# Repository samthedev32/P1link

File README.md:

# P1link
Cellural (NB-IoT) P1 Port Reader

## Hardware

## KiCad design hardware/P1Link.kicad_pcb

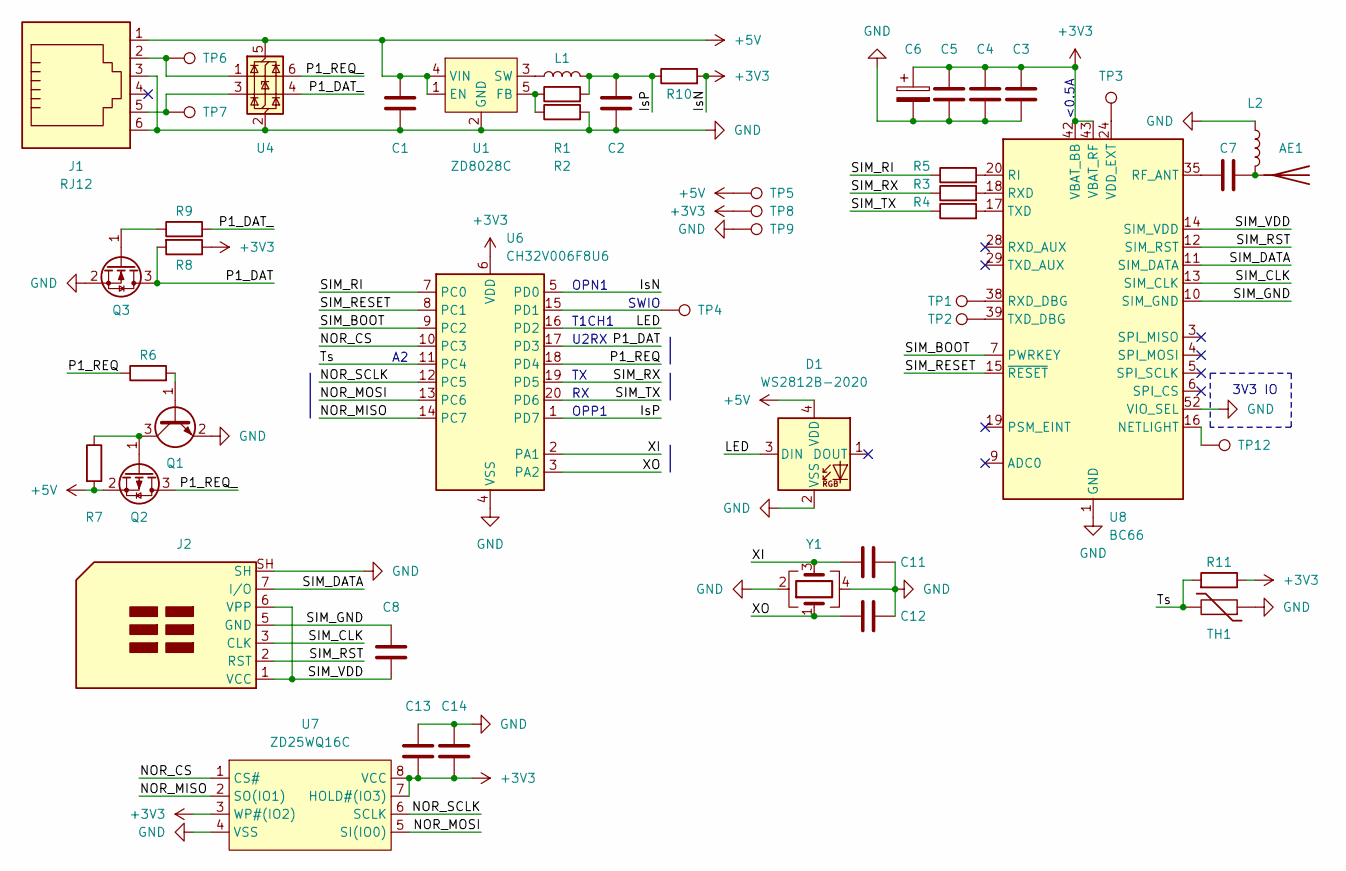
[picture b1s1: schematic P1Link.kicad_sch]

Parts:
AE1: Antenna; Texas_SWRA416_868MHz_915MHz
C1, C2, C14: 10u; C_0402_1005Metric
C3: 22p; C_0402_1005Metric
C4, C5: 100p; C_0402_1005Metric
C6: 100u; C_1206_3216Metric
C7: 1p; C_0402_1005Metric
C8, C13: 100n; C_0402_1005Metric
C11, C12: 8p; C_0402_1005Metric
D1: WS2812B-2020; LED_WS2812B-2020_PLCC4_2.0x2.0mm; JLCPCB Part# C965555
J1: RJ12; RJ25_Wayconn_MJEA-660X1_Horizontal; JLCPCB Part# C77859
J2: SIM_Card_Shielded; XUNPU_SMN-305; JLCPCB Part# C720512
L1: 4.7u; L_0402_1005Metric
L2: 12n; L_0402_1005Metric
Q1: Q_NPN_BEC; SOT-23; JLCPCB Part# C39280
Q2: Q_PMOS_GSD; SOT-23; JLCPCB Part# C5261052
Q3: Q_NMOS_GSD; SOT-23; JLCPCB Part# C4748714
R1: 261k; R_0402_1005Metric
R2: 59k; R_0402_1005Metric
R3, R4, R5: 1k; R_0402_1005Metric
R6: 1k - 10k; R_0402_1005Metric
R7: 10k - 100k; R_0402_1005Metric
R8: 4.7k - 10k; R_0402_1005Metric
R9: 100-1k; R_0402_1005Metric
R10: 100m; R_0402_1005Metric; JLCPCB Part# C1882657
R11: 10k; R_0402_1005Metric
TH1: 10k; R_0402_1005Metric; JLCPCB Part# C89601
TP1: RXD_DBG; TestPoint_Pad_D1.0mm
TP2: TXD_DBG; TestPoint_Pad_D1.0mm
TP3: VDD_EXT; TestPoint_Pad_D1.0mm
TP4: SWIO; TestPoint_Pad_D1.0mm
TP5: 5V; TestPoint_Pad_D1.0mm
TP6: P1REQ; TestPoint_Pad_D1.0mm
TP7: P1DAT; TestPoint_Pad_D1.0mm
TP8: 3V3; TestPoint_Pad_D1.0mm
TP9: GND; TestPoint_Pad_D1.0mm
TP12: NETLIGHT; TestPoint_Pad_D1.0mm
U1: ZD8028C; SOT-23-5; JLCPCB Part# C2928932
U4: USBLC6-2SC6; SOT-23-6; JLCPCB Part# C2687116
U6: CH32V006F8U6; QFN-20-1EP_3x3mm_P0.4mm_EP1.65x1.65mm; JLCPCB Part# C42431288
U7: ZD25WQ16C; Winbond_USON-8-1EP_3x2mm_P0.5mm_EP0.2x1.6mm; JLCPCB Part# C7304007
U8: BC66; Quectel_BC66; JLCPCB Part# C5140591
Y1: 24M; Crystal_SMD_2016-4Pin_2.0x1.6mm; JLCPCB Part# C2965580

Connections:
+3V3: C3.1, C4.1, C5.1, C6.1, C13.2, C14.2, R8.1, R10.2, R11.1, TP8.1, U6.5 (PD0), U6.6 (VDD), U7.3 (WP#(IO2)), U7.7 (HOLD#(IO3)), U7.8 (VCC), U8.42 (VBAT_BB), U8.43 (VBAT_RF)
+5V: C1.1, D1.4 (VDD), J1.1, Q2.2 (S), R7.2, TP5.1, U1.1 (EN), U1.4 (VIN), U4.5 (VBUS)
/IsP: C2.1, L1.2, R1.2, R10.1, U6.1 (PD7)
/LED: D1.3 (DIN), U6.16 (PD2)
/NOR_CS: U6.10 (PC3), U7.1 (CS#)
/NOR_MISO: U6.14 (PC7), U7.2 (SO(IO1))
/NOR_MOSI: U6.13 (PC6), U7.5 (SI(IO0))
/NOR_SCLK: U6.12 (PC5), U7.6 (SCLK)
/P1_DAT: Q3.3 (D), R8.2, U6.17 (PD3)
/P1_DAT_: R9.2, U4.4 (I/O2)
/P1_REQ: R6.1, U6.18 (PD4)
/P1_REQ_: Q2.3 (D), U4.6 (I/O1)
/SIM_BOOT: U6.9 (PC2), U8.7 (PWRKEY)
/SIM_CLK: J2.3 (CLK), U8.13 (SIM_CLK)
/SIM_DATA: J2.7 (I/O), U8.11 (SIM_DATA)
/SIM_GND: C8.1, J2.5 (GND), U8.10 (SIM_GND)
/SIM_RESET: U6.8 (PC1), U8.15 (~RESET)
/SIM_RI: R5.1, U6.7 (PC0)
/SIM_RST: J2.2 (RST), U8.12 (SIM_RST)
/SIM_RX: R3.1, U6.19 (PD5)
/SIM_TX: R4.1, U6.20 (PD6)
/SIM_VDD: C8.2, J2.1 (VCC), J2.6 (VPP), U8.14 (SIM_VDD)
/Ts: R11.2, TH1.2, U6.11 (PC4)
/XI: C11.1, U6.2 (PA1), Y1.3
/XO: C12.1, U6.3 (PA2), Y1.1
GND: C1.2, C2.2, C3.2, C4.2, C5.2, C6.2, C11.2, C12.2, C13.1, C14.1, D1.2 (VSS), J1.3, J1.6, J2.SH, L2.1, Q1.2 (E), Q3.2 (S), R2.2, TH1.1, TP9.1, U1.2 (GND), U4.2 (GND), U6.4 (VSS), U6.21 (VSS), U7.4 (VSS), U7.9 (TP), U8.1 (GND), U8.27 (GND), U8.34 (GND), U8.36 (GND), U8.37 (GND), U8.40 (GND), U8.41 (GND), U8.52 (VIO_SEL), Y1.2, Y1.4
unnamed: AE1.1 (A), C7.2, L2.2
unnamed: J1.2, TP6.1, U4.1 (I/O1)
unnamed: J1.5, TP7.1, U4.3 (I/O2)
unnamed: Q1.1 (B), R6.2
unnamed: Q1.3 (C), Q2.1 (G), R7.1
unnamed: Q3.1 (G), R9.1
unnamed: R1.1, R2.1, U1.5 (FB)
unnamed: L1.1, U1.3 (SW)
unnamed: TP4.1, U6.15 (PD1)
unnamed: TP12.1, U8.16 (NETLIGHT)
unnamed: C7.1, U8.35 (RF_ANT)
unnamed: R5.2, U8.20 (RI)
unnamed: R3.2, U8.18 (RXD)
unnamed: TP1.1, U8.38 (RXD_DBG)
unnamed: R4.2, U8.17 (TXD)
unnamed: TP2.1, U8.39 (TXD_DBG)
unnamed: TP3.1, U8.24 (VDD_EXT)

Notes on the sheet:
U2RX
T1CH1
<0.5A
OPP1
OPN1
SWIO
3V3 IO

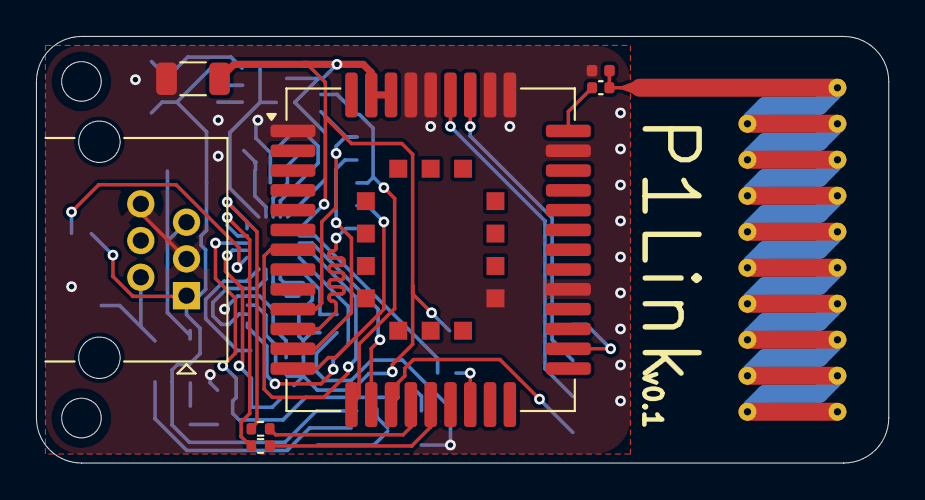
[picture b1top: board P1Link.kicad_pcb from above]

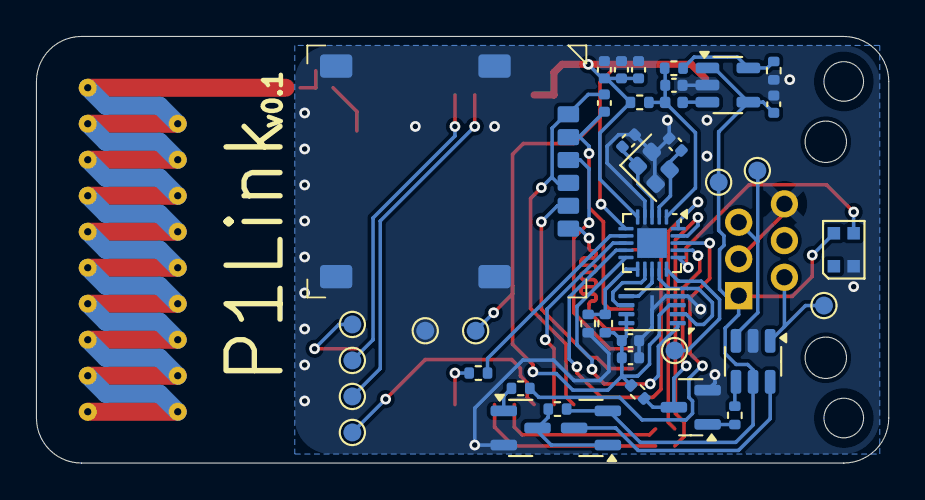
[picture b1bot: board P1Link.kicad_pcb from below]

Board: 2 copper layers, 47.3 x 23.7 mm, 49 parts (41 on the bottom side), 43 nets.

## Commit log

2025-09-27 schematics, layout & routing start
2025-09-28 V0.1 finished
